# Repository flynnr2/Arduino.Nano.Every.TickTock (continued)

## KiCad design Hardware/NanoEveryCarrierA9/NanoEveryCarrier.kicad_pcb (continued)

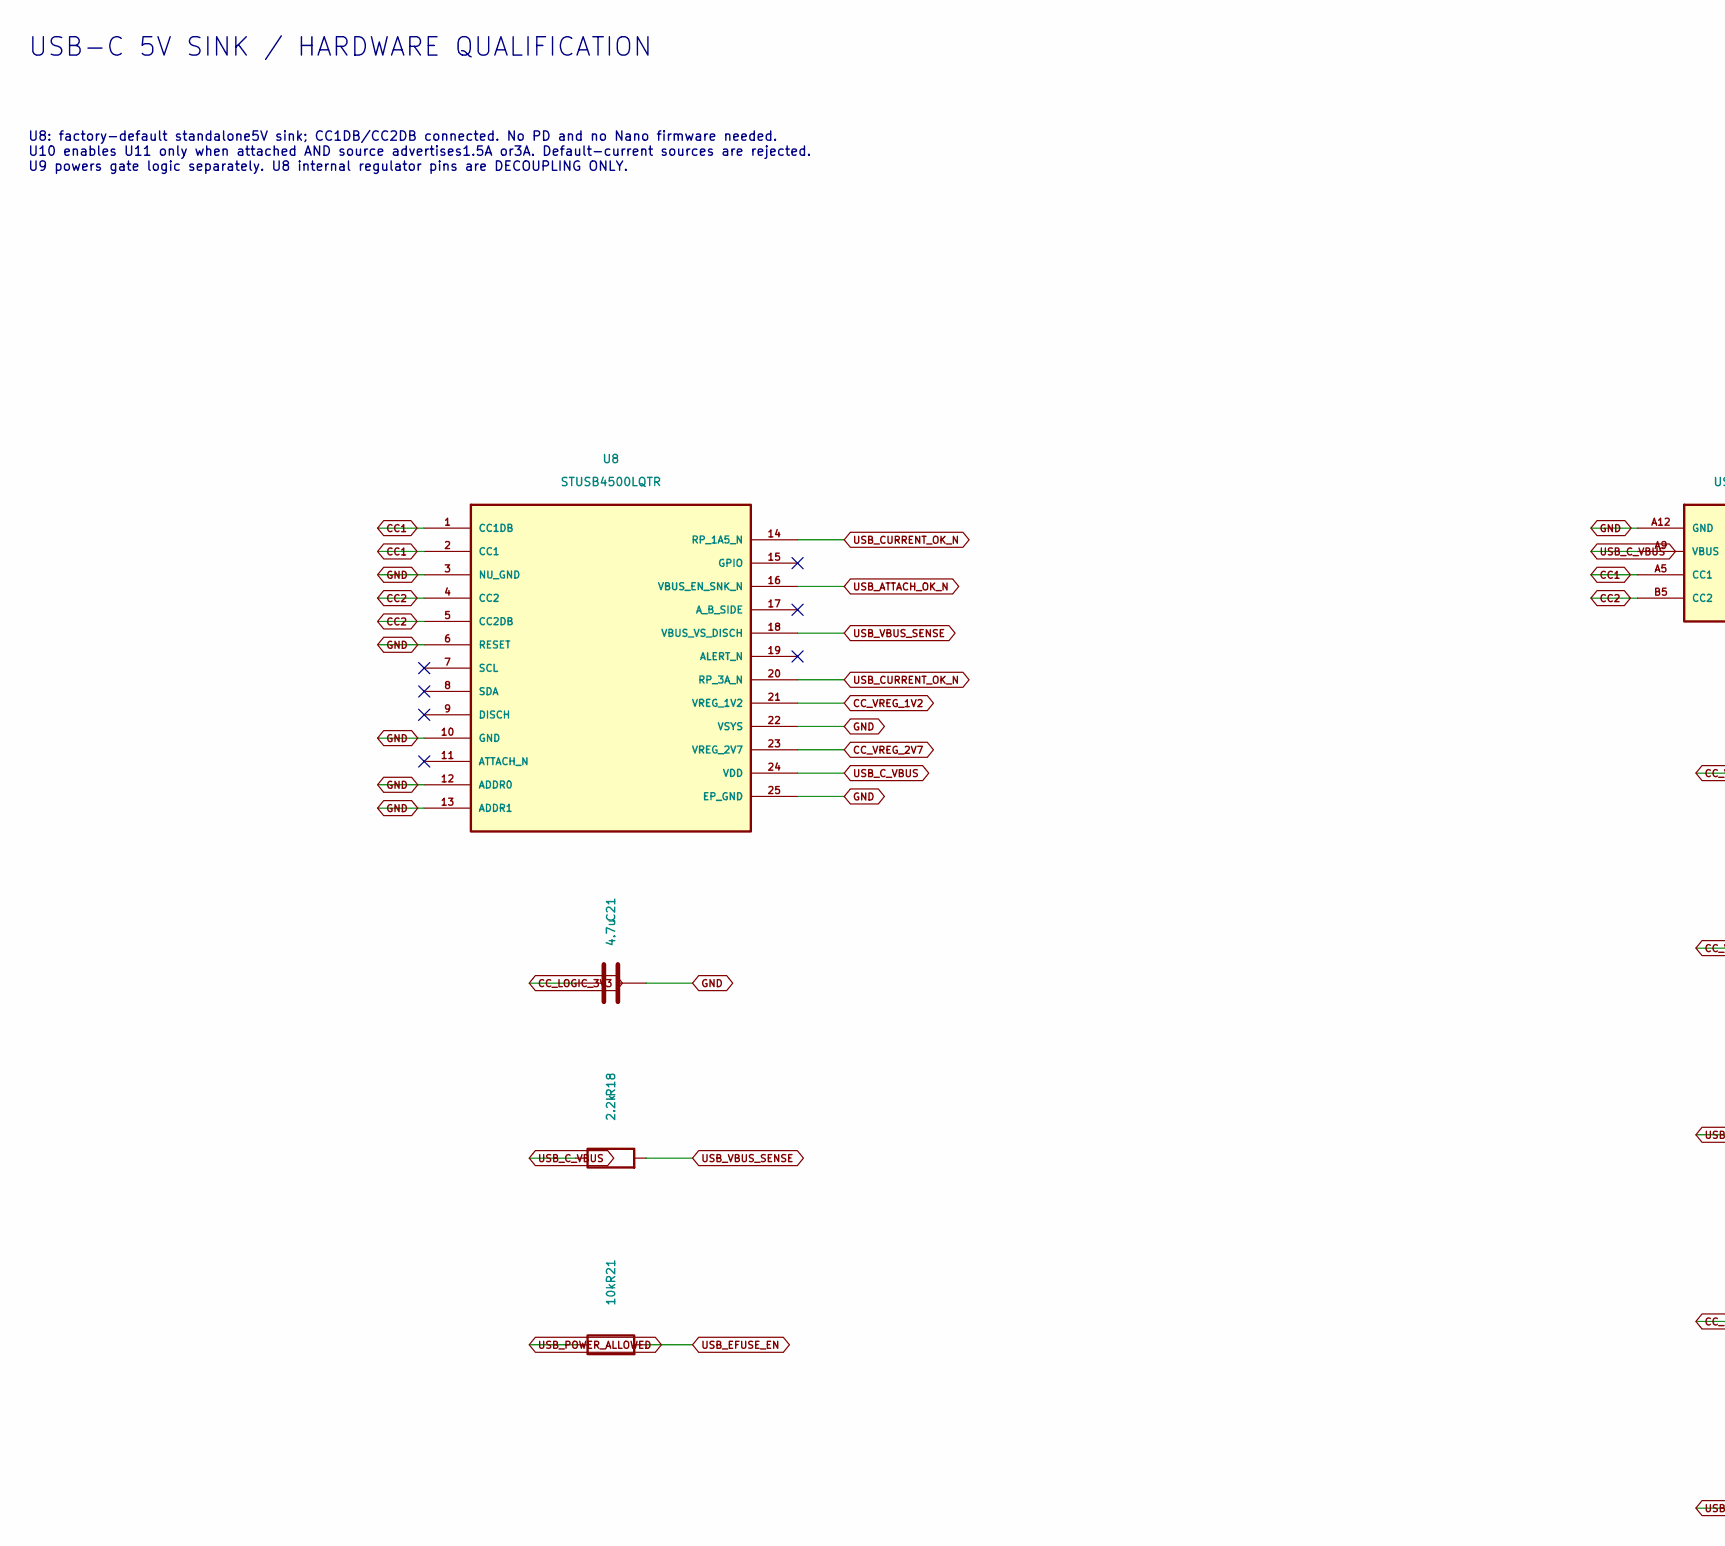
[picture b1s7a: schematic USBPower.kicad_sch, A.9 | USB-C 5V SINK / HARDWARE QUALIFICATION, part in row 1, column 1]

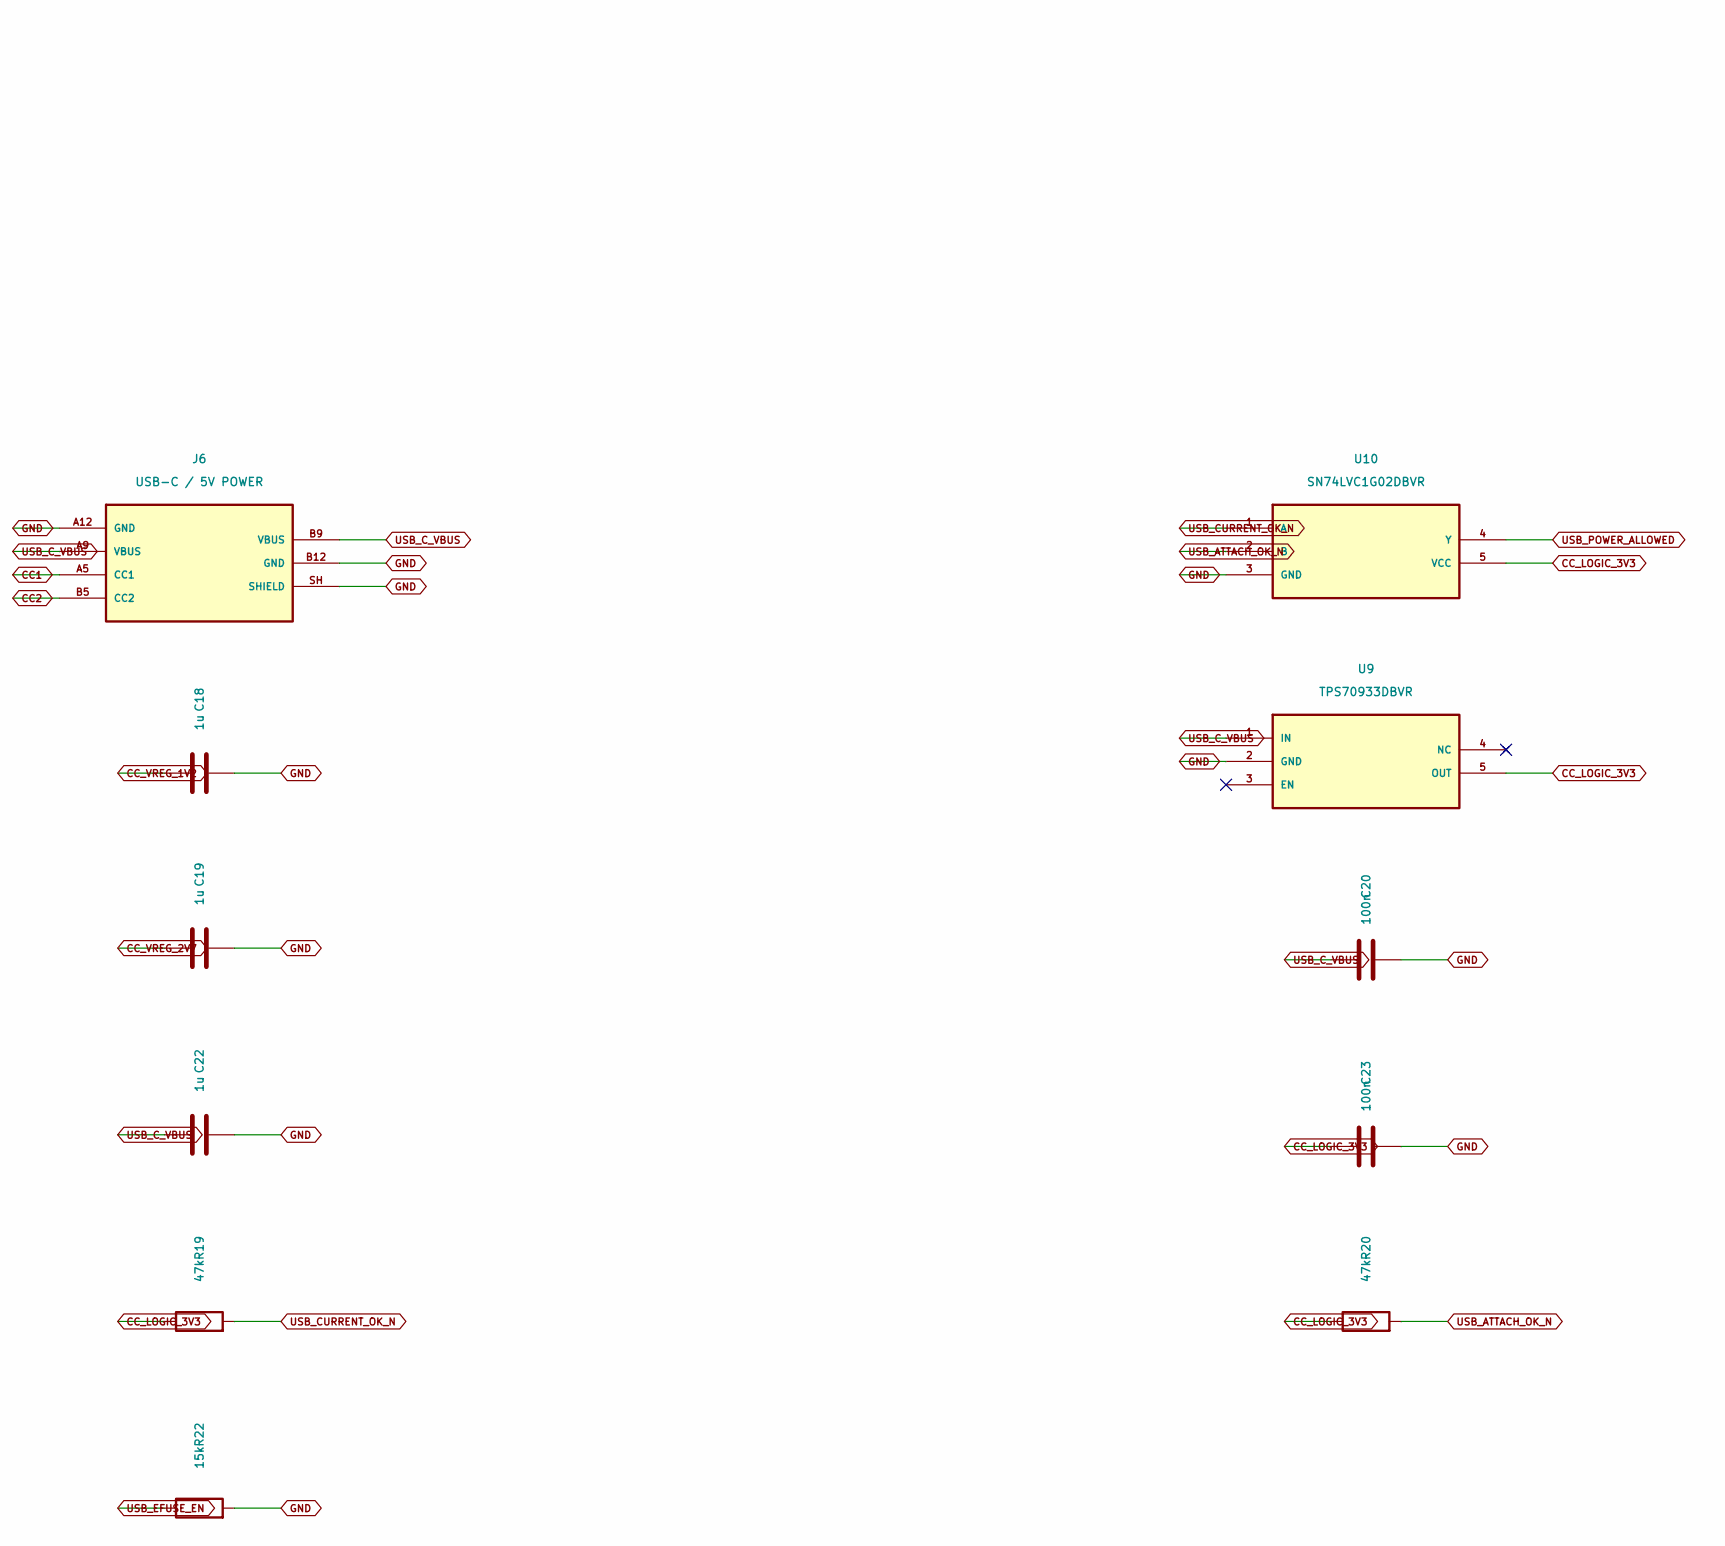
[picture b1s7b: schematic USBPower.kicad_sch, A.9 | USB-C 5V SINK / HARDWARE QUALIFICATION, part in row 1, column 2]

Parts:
C18, C19: 1u; C_0805_2012Metric; MPN GRM21BR71C105KA01L
C20, C23: 100n; C_0805_2012Metric; MPN GRM21BR71H104KA01L
C21: 4.7u; C_0805_2012Metric; MPN GRM21BR71C475KA73L
C22: 1u; C_0805_2012Metric; MPN GRM21BR71H105KA12L
J6: USB-C / 5V POWER; USB_C_Receptacle_GCT_USB4125-xx-x-0190_6P_TopMnt_Horizontal; MPN USB4125-GF-A-0190
R18: 2.2k; R_1206_3216Metric_Pad1.30x1.75mm_HandSolder; MPN RC1206FR-072K2L
R19, R20: 47k; R_0805_2012Metric; MPN RC0805FR-0747KL
R21: 10k; R_0805_2012Metric; MPN RC0805FR-0710KL
R22: 15k; R_0805_2012Metric; MPN RC0805FR-0715KL
U8: STUSB4500LQTR; QFN-24-1EP_4x4mm_P0.5mm_EP2.6x2.6mm; MPN STUSB4500LQTR
U9: TPS70933DBVR; SOT-23-5; MPN TPS70933DBVR
U10: SN74LVC1G02DBVR; SOT-23-5; MPN SN74LVC1G02DBVR

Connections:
CC1: J6.A5 (CC1), U8.1 (CC1DB), U8.2 (CC1)
CC2: J6.B5 (CC2), U8.4 (CC2), U8.5 (CC2DB)
CC_LOGIC_3V3: C21.1, C23.1, R19.1, R20.1, U9.5 (OUT), U10.5 (VCC)
CC_VREG_1V2: C18.1, U8.21 (VREG_1V2)
CC_VREG_2V7: C19.1, U8.23 (VREG_2V7)
GND: C18.2, C19.2, C20.2, C21.2, C22.2, C23.2, J6.A12 (GND), J6.B12 (GND), J6.SH (SHIELD), R22.2, U8.3 (NU_GND), U8.6 (RESET), U8.10 (GND), U8.12 (ADDR0), U8.13 (ADDR1), U8.22 (VSYS), U8.25 (EP_GND), U9.2 (GND), U10.3 (GND); also elsewhere on the board
USB_ATTACH_OK_N: R20.2, U8.16 (VBUS_EN_SNK_N), U10.2 (B)
USB_CURRENT_OK_N: R19.2, U8.14 (RP_1A5_N), U8.20 (RP_3A_N), U10.1 (A)
USB_C_VBUS: C20.1, C22.1, J6.A9 (VBUS), J6.B9 (VBUS), R18.1, U8.24 (VDD), U9.1 (IN); also elsewhere on the board
USB_EFUSE_EN: R21.2, R22.1; also elsewhere on the board
USB_POWER_ALLOWED: R21.1, U10.4 (Y)
USB_VBUS_SENSE: R18.2, U8.18 (VBUS_VS_DISCH)

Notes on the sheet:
USB-C 5V SINK / HARDWARE QUALIFICATION
U8: factory-default standalone5V sink; CC1DB/CC2DB connected. No PD and no Nano firmware needed. U10 enables U11 only when attached AND source advertises1.5A or3A. Default-current sources are rejected. U9 powers gate logic separately. U8 internal regulator pins are DECOUPLING ONLY.

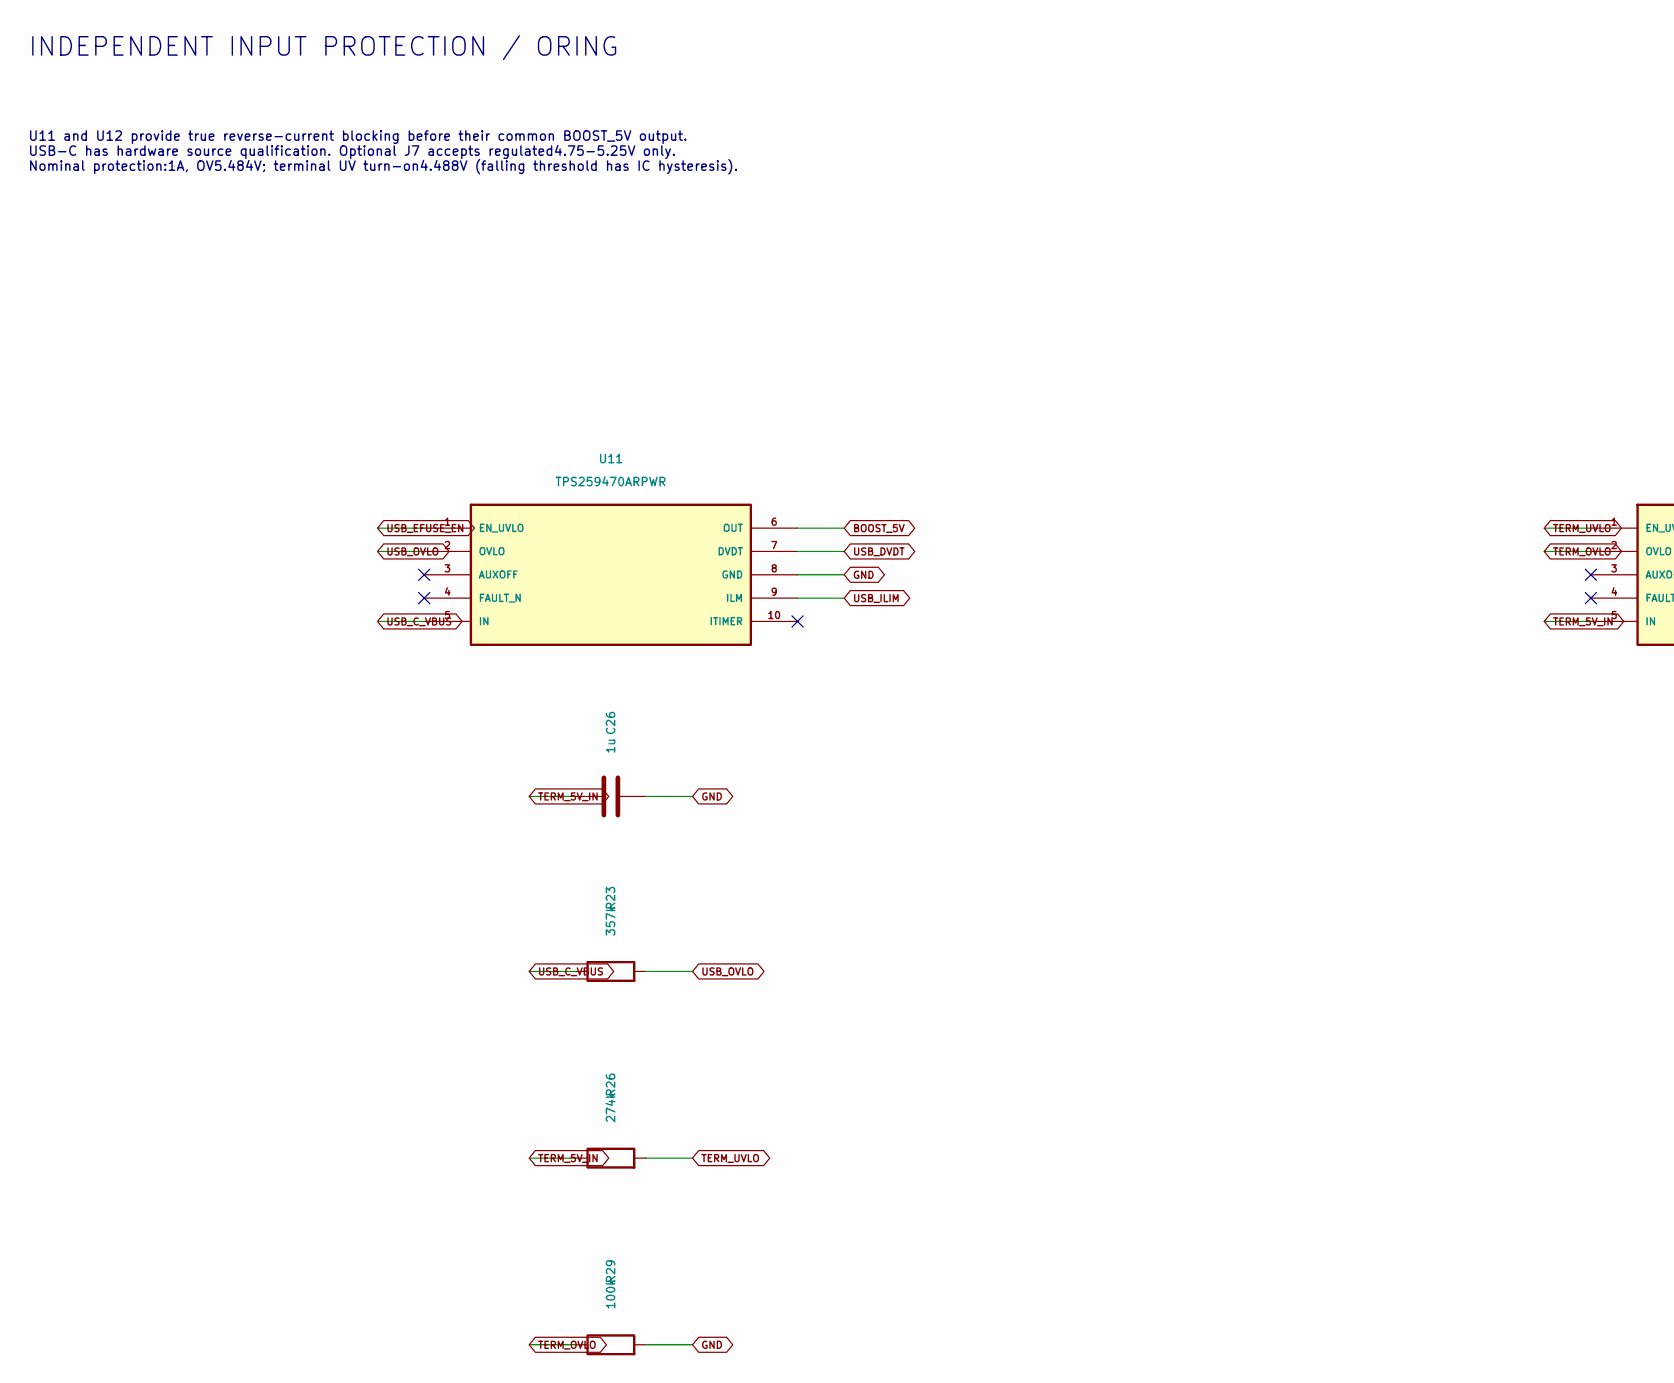
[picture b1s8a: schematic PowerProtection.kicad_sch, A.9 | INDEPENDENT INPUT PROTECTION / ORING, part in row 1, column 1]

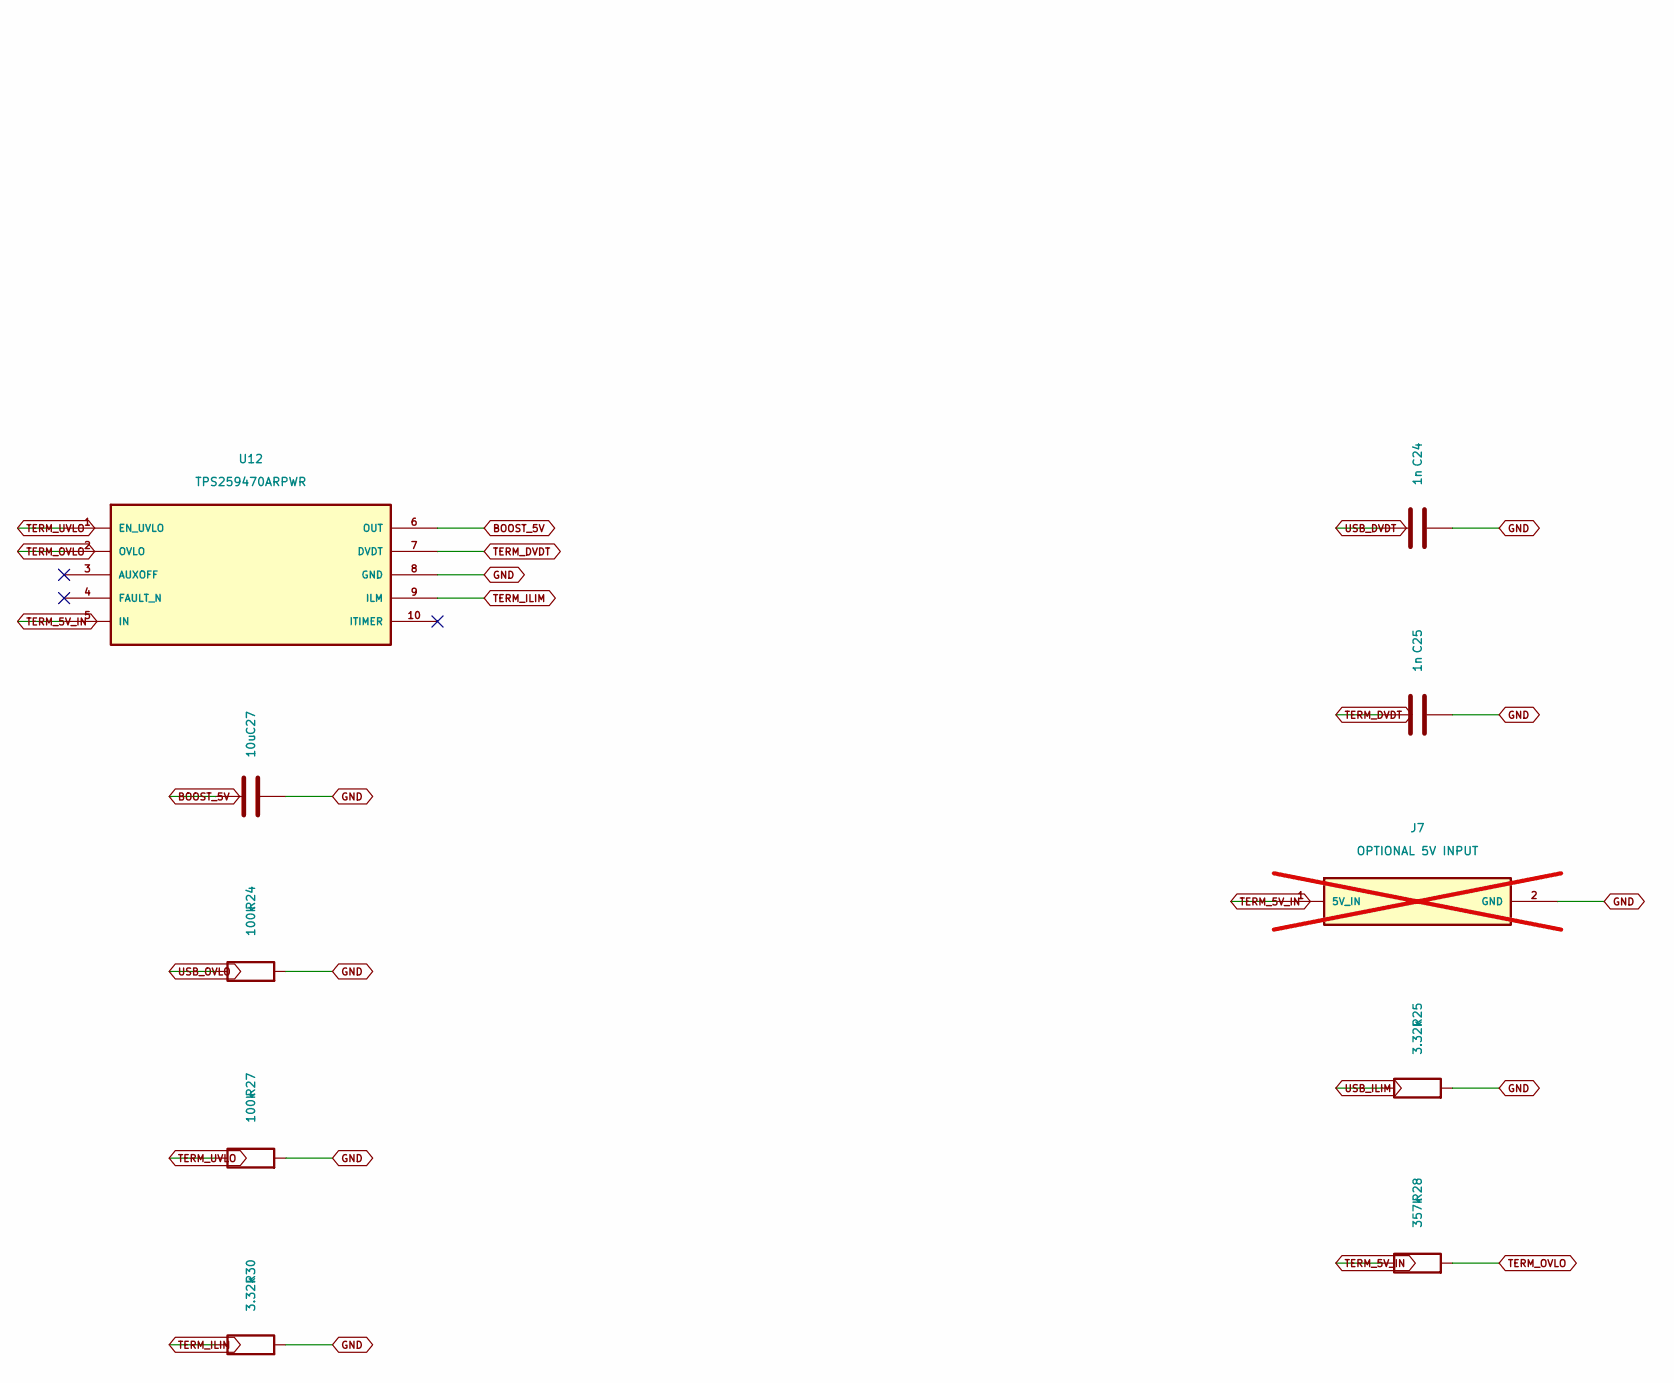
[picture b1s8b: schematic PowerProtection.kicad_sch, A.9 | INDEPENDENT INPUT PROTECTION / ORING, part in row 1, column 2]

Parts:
C24, C25: 1n; C_0805_2012Metric; MPN GRM21B5C1H102JA01L
C26: 1u; C_0805_2012Metric; MPN GRM21BR71H105KA12L
C27: 10u; C_0805_2012Metric; MPN GRM21BR61C106KE15L
J7: OPTIONAL 5V INPUT; TerminalBlock_Phoenix_MKDS-1,5-2-5.08_1x02_P5.08mm_Horizont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; MPN 1715721; not fitted
R23, R28: 357k; R_0805_2012Metric; MPN RC0805FR-07357KL
R24, R27, R29: 100k; R_0805_2012Metric; MPN RC0805FR-07100KL
R25, R30: 3.32k; R_0805_2012Metric; MPN RC0805FR-073K32L
R26: 274k; R_0805_2012Metric; MPN RC0805FR-07274KL
U11, U12: TPS259470ARPWR; TI_RPW0010A; MPN TPS259470ARPWR

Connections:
BOOST_5V: C27.1, U11.6 (OUT), U12.6 (OUT); also elsewhere on the board
GND: C24.2, C25.2, C26.2, C27.2, J7.2 (GND), R24.2, R25.2, R27.2, R29.2, R30.2, U11.8 (GND), U12.8 (GND); also elsewhere on the board
TERM_5V_IN: C26.1, J7.1 (5V_IN), R26.1, R28.1, U12.5 (IN)
TERM_DVDT: C25.1, U12.7 (DVDT)
TERM_ILIM: R30.1, U12.9 (ILM)
TERM_OVLO: R28.2, R29.1, U12.2 (OVLO)
TERM_UVLO: R26.2, R27.1, U12.1 (EN_UVLO)
USB_C_VBUS: R23.1, U11.5 (IN); also elsewhere on the board
USB_DVDT: C24.1, U11.7 (DVDT)
USB_EFUSE_EN: U11.1 (EN_UVLO); also elsewhere on the board
USB_ILIM: R25.1, U11.9 (ILM)
USB_OVLO: R23.2, R24.1, U11.2 (OVLO)

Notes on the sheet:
INDEPENDENT INPUT PROTECTION / ORING
U11 and U12 provide true reverse-current blocking before their common BOOST_5V output. USB-C has hardware source qualification. Optional J7 accepts regulated4.75-5.25V only. Nominal protection:1A, OV5.484V; terminal UV turn-on4.488V (falling threshold has IC hysteresis).

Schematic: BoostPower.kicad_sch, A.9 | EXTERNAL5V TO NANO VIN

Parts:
C28: 3.3n; C_0805_2012Metric; MPN GRM21B5C1H332JA01L
C29: 100n; C_0805_2012Metric; MPN GRM21BR71H104KA01L
C30, C32: 22u; C_1206_3216Metric; MPN GRM31CR71C226KE15L
C31: 1u; C_0805_2012Metric; MPN GRM21BR71C105KA01L
D2: SS24; D_SMA; MPN SS24-E3/61T
D3: SS14; D_SMA; MPN SS14-E3/61T
JP1: EXT VIN ENABLE; PinHeader_1x02_P2.54mm_Vertical; MPN TSW-102-07-G-S
L1: 4.7uH / 2.5A; Wurth_7447785004; MPN 7447785004
R31: 100k; R_0805_2012Metric; MPN RC0805FR-07100KL
R32: 18.2k; R_0805_2012Metric; MPN RC0805FR-0718K2L
R33: 13k; R_0805_2012Metric; MPN RC0805FR-0713KL
U13: TPS61085PWR; TSSOP-8_4.4x3mm_P0.65mm; MPN TPS61085PWR

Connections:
BOOST_5V: C31.1, L1.1, U13.3 (EN), U13.6 (IN), U13.7 (FREQ); also elsewhere on the board
BOOST_8V: C30.1, C32.1, D2.1 (K), D3.2 (A), R31.1
BOOST_COMP: R33.1, U13.1 (COMP)
BOOST_COMP_C: C28.1, R33.2
BOOST_FB: R31.2, R32.1, U13.2 (FB)
BOOST_SS: C29.1, U13.8 (SS)
BOOST_SW: D2.2 (A), L1.2, U13.5 (SW)
EXT_VIN_FEED: D3.1 (K), JP1.1
GND: C28.2, C29.2, C30.2, C31.2, C32.2, R32.2, U13.4 (PGND); also elsewhere on the board
NANO_VIN: JP1.2; also elsewhere on the board

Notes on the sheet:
EXTERNAL5V TO NANO VIN
Boost8.04V; D3 blocks any Nano VIN voltage from feeding the boost capacitors or converter. Nano USB powers its5V rail through Nano D2, separately from the VIN buck input. JP1 disconnects external VIN feed only. USB load/rail voltage and transfer continuity need bench acceptance.

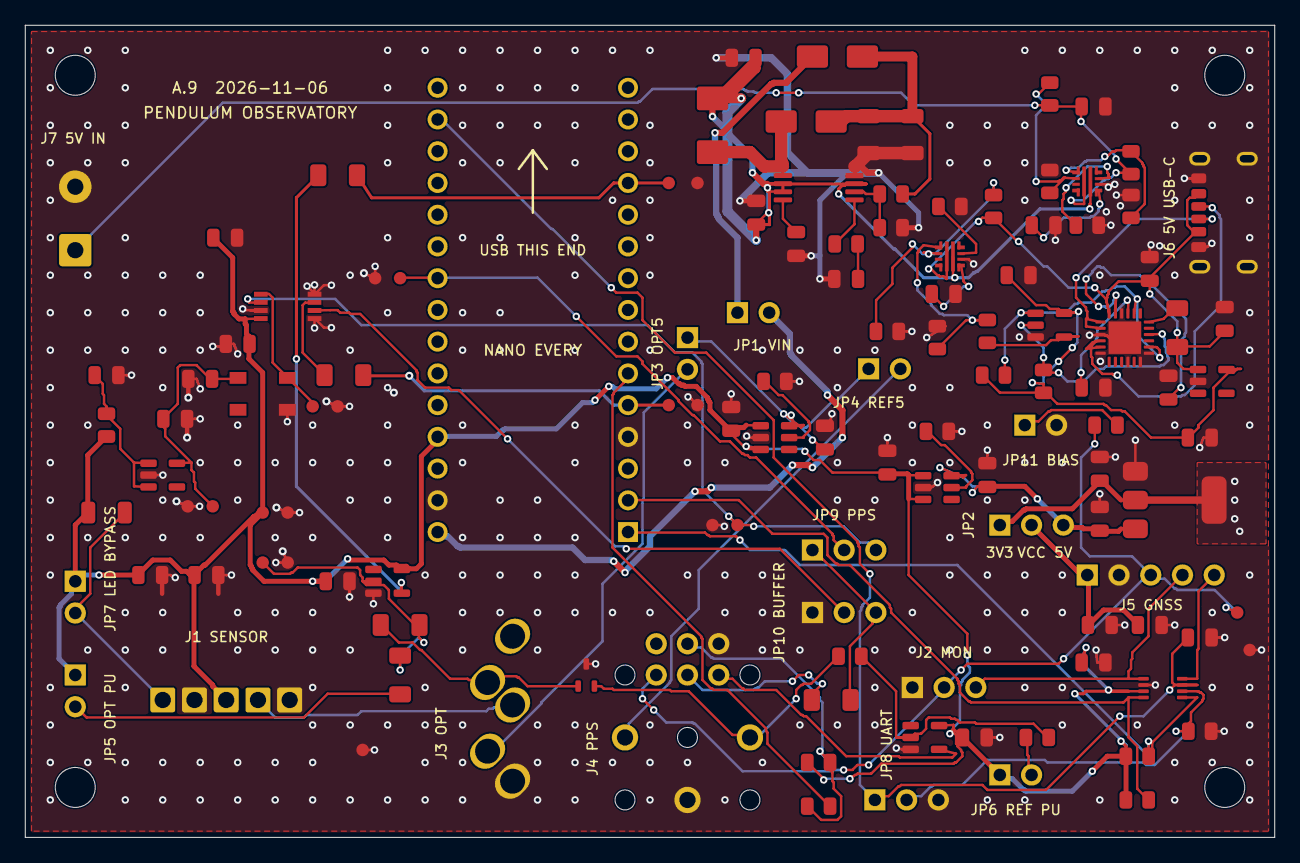
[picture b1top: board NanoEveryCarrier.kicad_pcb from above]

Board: 2 copper layers, 100.0 x 65.0 mm, 128 parts (0 on the bottom side), 69 nets.

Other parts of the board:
H1, H2, H3, H4: MountingHole_3.2mm_M3
TP11, TP12, TP13, TP14, TP15, TP16, TP17, TP18, TP19: GND; TestPoint_Pad_D1.0mm

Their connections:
GND: TP11.1, TP12.1, TP13.1, TP14.1, TP15.1, TP16.1, TP17.1, TP18.1, TP19.1; also elsewhere on the board

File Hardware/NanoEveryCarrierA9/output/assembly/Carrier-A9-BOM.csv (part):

References,Quantity,Value,Manufacturer,MPN,Footprint,Populate,Assembly notes
A1,2,Arduino_Nano_Every,Samtec,SSW-115-01-G-S,Carrier:Nano_Every_Sockets,FIT,"TWO socket strips; Nano not included in PCB parts. Fit TWO female 1x15 sockets. Baseline customer Nano reuse; separately quote genuine Arduino ABX00033 with headers inserted into sockets, no direct module soldering."
"C1, C3, C5, C7, C11, C14, C15, C17, C20, C23, C29",11,100n,Murata,GRM21BR71H104KA01L,Carrier:C_0805_2012Metric,FIT,100 nF 50 V X7R 0805; Local U3 bypass; 50V X7R.; 100nF UART translator bypass; place at U5 supply pin and local ground return.; Ceramic; effective capacitance must meet regulator requirements
"C2, C6, C8, C9, C10, C12, C13, C18, C19, C31, C33",11,1u,Murata,GRM21BR71C105KA01L,Carrier:C_0805_2012Metric,FIT,"1 uF 16 V X7R 0805; 1uF GNSS switch input bypass, 16V X7R; place close to U4.; 1uF GNSS switch output bypass, 16V X7R; receiver supplies local bulk decoupling.; U2 input bypass; 16V X7R.; U2 output bypass; 16V X7R.; Ceramic; effective capacitance must meet regulator requirements; GNSS regulator local bypass. X7R/X5R;C34 effective capacitance must exceed0.5uF after bias,tolerance and temperature."
"C4, C21, C34",3,4.7u,Murata,GRM21BR71C475KA73L,Carrier:C_0805_2012Metric,FIT,"4.7 uF 16 V X7R 0805; Ceramic; effective capacitance must meet regulator requirements; GNSS regulator local bypass. X7R/X5R;C34 effective capacitance must exceed0.5uF after bias,tolerance and temperature."
"C16, C27",2,10u,Murata,GRM21BR61C106KE15L,Carrier:C_0805_2012Metric,FIT,Ceramic; effective capacitance must meet regulator requirements
"C22, C26",2,1u,Murata,GRM21BR71H105KA12L,Carrier:C_0805_2012Metric,FIT,1uF 50V X7R; input-side overvoltage withstand.
"C24, C25",2,1n,Murata,GRM21B5C1H102JA01L,Carrier:C_0805_2012Metric,FIT,Ceramic; effective capacitance must meet regulator requirements
C28,1,3.3n,Murata,GRM21B5C1H332JA01L,Carrier:C_0805_2012Metric,FIT,Ceramic; effective capacitance must meet regulator requirements
"C30, C32",2,22u,Murata,GRM31CR71C226KE15L,Carrier:C_1206_3216Metric,FIT,Ceramic; effective capacitance must meet regulator requirements
D1,1,TPD2E2U06DCKR,Texas Instruments,TPD2E2U06DCKR,Carrier:SOT-323_SC-70,FIT,Two low-capacitance ESD channels at jack rings; not a DC overvoltage limiter.
D2,1,SS24,Vishay,SS24-E3/61T,Carrier:D_SMA,FIT,
D3,1,SS14,Vishay,SS14-E3/61T,Carrier:D_SMA,FIT,
J1,1,PENDULUM / SCREW,Wurth Elektronik,691210910005,Carrier:Wurth_691210910005,FIT,
J2,1,GNSS MONITOR,Samtec,TSW-103-07-G-S,Carrier:PinHeader_1x03_P2.54mm_Vertical,FIT,
J3,1,OPTO TRS,Same Sky,SJ1-3535NG,Carrier:Jack_3.5mm_CUI_SJ1-3535NG_Horizontal_CircularHoles,FIT,Tip +5V output; ring optical; sleeve GND. RN selects J1 when unplugged.
J4,1,EXT PPS / DETECT,Kycon,STX-3100-9N,Carrier:Jack_3.5mm_Kycon_STX-3100-9N,FIT,"Isolated DPDT: empty 7-6 (GNSS), inserted 7-8 (ring); 10-11 grounds detect on insertion. 9 NC. No substitution with SJ1-3535NG."
J5,1,GNSS / SELECTED VCC,Samtec,TSW-105-07-G-S,Carrier:PinHeader_1x05_P2.54mm_Vertical,FIT,J5/1 is selected GNSS VCC from JP2. Default3.3V; fitJP2 2-3 for5V only for a qualified receiver. J5 signals remain nominal3.3V.
J6,1,USB-C / 5V POWER,GCT,USB4125-GF-A-0190,Carrier:USB_C_Receptacle_GCT_USB4125-xx-x-0190_6P_TopMnt_Horizontal,FIT,1.90mm shell stakes for1.6mm PCB. Power-only6P; no data pins. Do not substitute1.00mm stake variant.
J7,1,OPTIONAL 5V INPUT,Phoenix Contact,1715721,"Carrier:TerminalBlock_Phoenix_MKDS-1,5-2-5.08_1x02_P5.08mm_Horizontal",OPTIONAL / DNP,"Optional connector, NOT fitted by default. Protection circuit remains fitted."
JP1,1,EXT VIN ENABLE,Samtec,TSW-102-07-G-S,Carrier:PinHeader_1x02_P2.54mm_Vertical,FIT,Fit shunt: boosted external supply to Nano VIN. Remove to disconnect external VIN feed; Nano USB can still power the carrier.
JP2,1,GNSS VCC / 3V3-5V,Samtec,TSW-103-07-G-S,Carrier:PinHeader_1x03_P2.54mm_Vertical,FIT,ONE shunt only:1-2=3.3V DEFAULT;2-3=5V;removed disconnectsJ5 power. Power off all attached equipment and discharge before moving. Never bridge all3. Remove before independently powering receiver.
JP3,1,OPTO POWER,Samtec,TSW-102-07-G-S,Carrier:PinHeader_1x02_P2.54mm_Vertical,FIT,Fit shunt: jack J3 tip power. Remove for independently powered accessory.
JP4,1,PPS POWER,Samtec,TSW-102-07-G-S,Carrier:PinHeader_1x02_P2.54mm_Vertical,FIT,Fit shunt: jack J4 tip power. Remove for independently powered accessory.
JP5,1,OPT PULLUP,Samtec,TSW-102-07-G-S,Carrier:PinHeader_1x02_P2.54mm_Vertical,FIT,Fit shunt: optical 10k pull-up to 5V. Fitted for installed OPB912; remove for a qualified push-pull or separately pulled-up source.
JP6,1,REF PULLUP,Samtec,TSW-102-07-G-S,Carrier:PinHeader_1x02_P2.54mm_Vertical,FIT,Fit shunt: external PPS 10k pull-up to 5V. Leave OPEN by default; fit only for a qualified open-collector source without its own pull-up.
JP7,1,LED RESISTOR BYPASS,Samtec,TSW-102-07-G-S,Carrier:PinHeader_1x02_P2.54mm_Vertical,FIT,FIT for existing external resistor-equipped lead. OPEN uses onboard R3 150 ohm for bare LED. Never fit bypass with a bare LED.
JP8,1,NANO UART ENABLE,Samtec,TSW-103-07-G-S,Carrier:PinHeader_1x03_P2.54mm_Vertical,FIT,JP8 1-2: Nano GNSS UART enabled (default). JP8 2-3: U5 disabled for receiver USB servicing. Change with all equipment powered off.
JP9,1,PPS source,Samtec,TSW-103-07-G-S,Carrier:PinHeader_1x03_P2.54mm_Vertical,FIT,Fit one shunt 2-3: buffered PPS. 1-2 direct is an optional measured comparison.
JP10,1,Buffer input,Samtec,TSW-103-07-G-S,Carrier:PinHeader_1x03_P2.54mm_Vertical,FIT,Fit one shunt 2-3: buffered PPS. Move JP9 and JP10 together with power off.
JP11,1,PPS BIAS,Samtec,TSW-102-07-G-S,Carrier:PinHeader_1x02_P2.54mm_Vertical,FIT,Leave OPEN by default. Fit only for a verified pull-down-tolerant source or no-source idle test.
L1,1,4.7uH / 2.5A,Wurth Elektronik,7447785004,Carrier:Wurth_7447785004,FIT,
R1,1,22R,Yageo,RC0805FR-0722RL,Carrier:R_0805_2012Metric,FIT,"1%, 0805"
R2,1,33R,Yageo,RC1206FR-0733RL,Carrier:R_1206_3216Metric_Pad1.30x1.75mm_HandSolder,FIT,"33 ohm 1%, 0.25 W; 1206 with extended solder pads; tune damping on bench"
R3,1,150R,Yageo,RC1206FR-07150RL,Carrier:R_1206_3216Metric,FIT,"150 ohm 1%, 0.25W LED limit. JP7 OPEN: bare LED. JP7 FITTED: bypass only for external resistor-equipped lead; fitted default for existing 145.5 ohm lead."
R4,1,0R,Yageo,RC1206JR-070RL,Carrier:R_1206_3216Metric_Pad1.30x1.75mm_HandSolder,FIT,0 ohm; 1206 with extended solder pads; optional optical damping position
"R5, R14, R16, R21",4,10k,Yageo,RC0805FR-0710KL,Carrier:R_0805_2012Metric,FIT,"10k PPS bias through JP11 only; JP11 open by default for boot-shared GNSS outputs.; J4 isolated detection pull-up; 10k to Nano 5V, independent of JP4.; 1%, 0805"
"R6, R8",2,100R,Yageo,RC1206FR-07100RL,Carrier:R_1206_3216Metric_Pad1.30x1.75mm_HandSolder,FIT,Optical series input protection; 1206 extended pads.; Selected PPS series input protection; 1206 extended pads; no pull-up.
R7,1,10k,Yageo,RC1206FR-0710KL,Carrier:R_1206_3216Metric_Pad1.30x1.75mm_HandSolder,FIT,Optical pull-up to 5V; supports open-collector optical outputs; sensor must tolerate pull-up.
R9,1,232k,Yageo,RC0805FR-07232KL,Carrier:R_0805_2012Metric,FIT,1% current-limit resistor; place close to U2 ILIM/GND.
R10,1,88.7k,Yageo,RC0805FR-0788K7L,Carrier:R_0805_2012Metric,FIT,88.7k 1% GNSS limit: 299mA nominal; 262-342mA published bounds. Target receiver/antenna <=200mA.
"R11, R12, R19, R20",4,47k,Yageo,RC0805FR-0747KL,Carrier:R_0805_2012Metric,FIT,"47k idle pull-up on 5V Nano UART only.; 1%, 0805"
"R13, R24, R27, R29, R31",5,100k,Yageo,RC0805FR-07100KL,Carrier:R_0805_2012Metric,FIT,"100k OE pull-down; translator disabled with JP8 shunt removed.; 1%, 0805"
R15,1,1k,Yageo,RC0805FR-071KL,Carrier:R_0805_2012Metric,FIT,"1k series protection between J4 detect and Nano D3. Firmware input, no internal pull-up required."
R17,1,100R,Yageo,RC0805FR-07100RL,Carrier:R_0805_2012Metric,FIT,"1%, 0805"
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
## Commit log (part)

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2026-03-13 major refactor
2026-03-21 Update
    The latest Nano Every repo update is a fairly substantial clean-up and capability upgrade rather than a small incremental change.
    The primary changes are:
    Architecture refactor / separation of concerns
    The codebase has been broken into clearer modules, with new components for capture handling, swing assembly, platform timing, status telemetry, and tunable management. In practice, this makes the fir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
    Custom platform timebase support
    There is now explicit support for running against a coherent TCB0-based platform time instead of relying on the Arduino timebase, including the option to disable the Arduino TCB3 millis/delay interru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
2026-03-21 Default to USB Serial
2026-03-28 refactor & extend
2026-03-28 clean up for innocents
2026-04-07 major cleanup & refactor
2026-04-07 first time user transparency
2026-05-01 refresh
2026-05-03 refactor
2026-05-06 block vs. !block sense correction
